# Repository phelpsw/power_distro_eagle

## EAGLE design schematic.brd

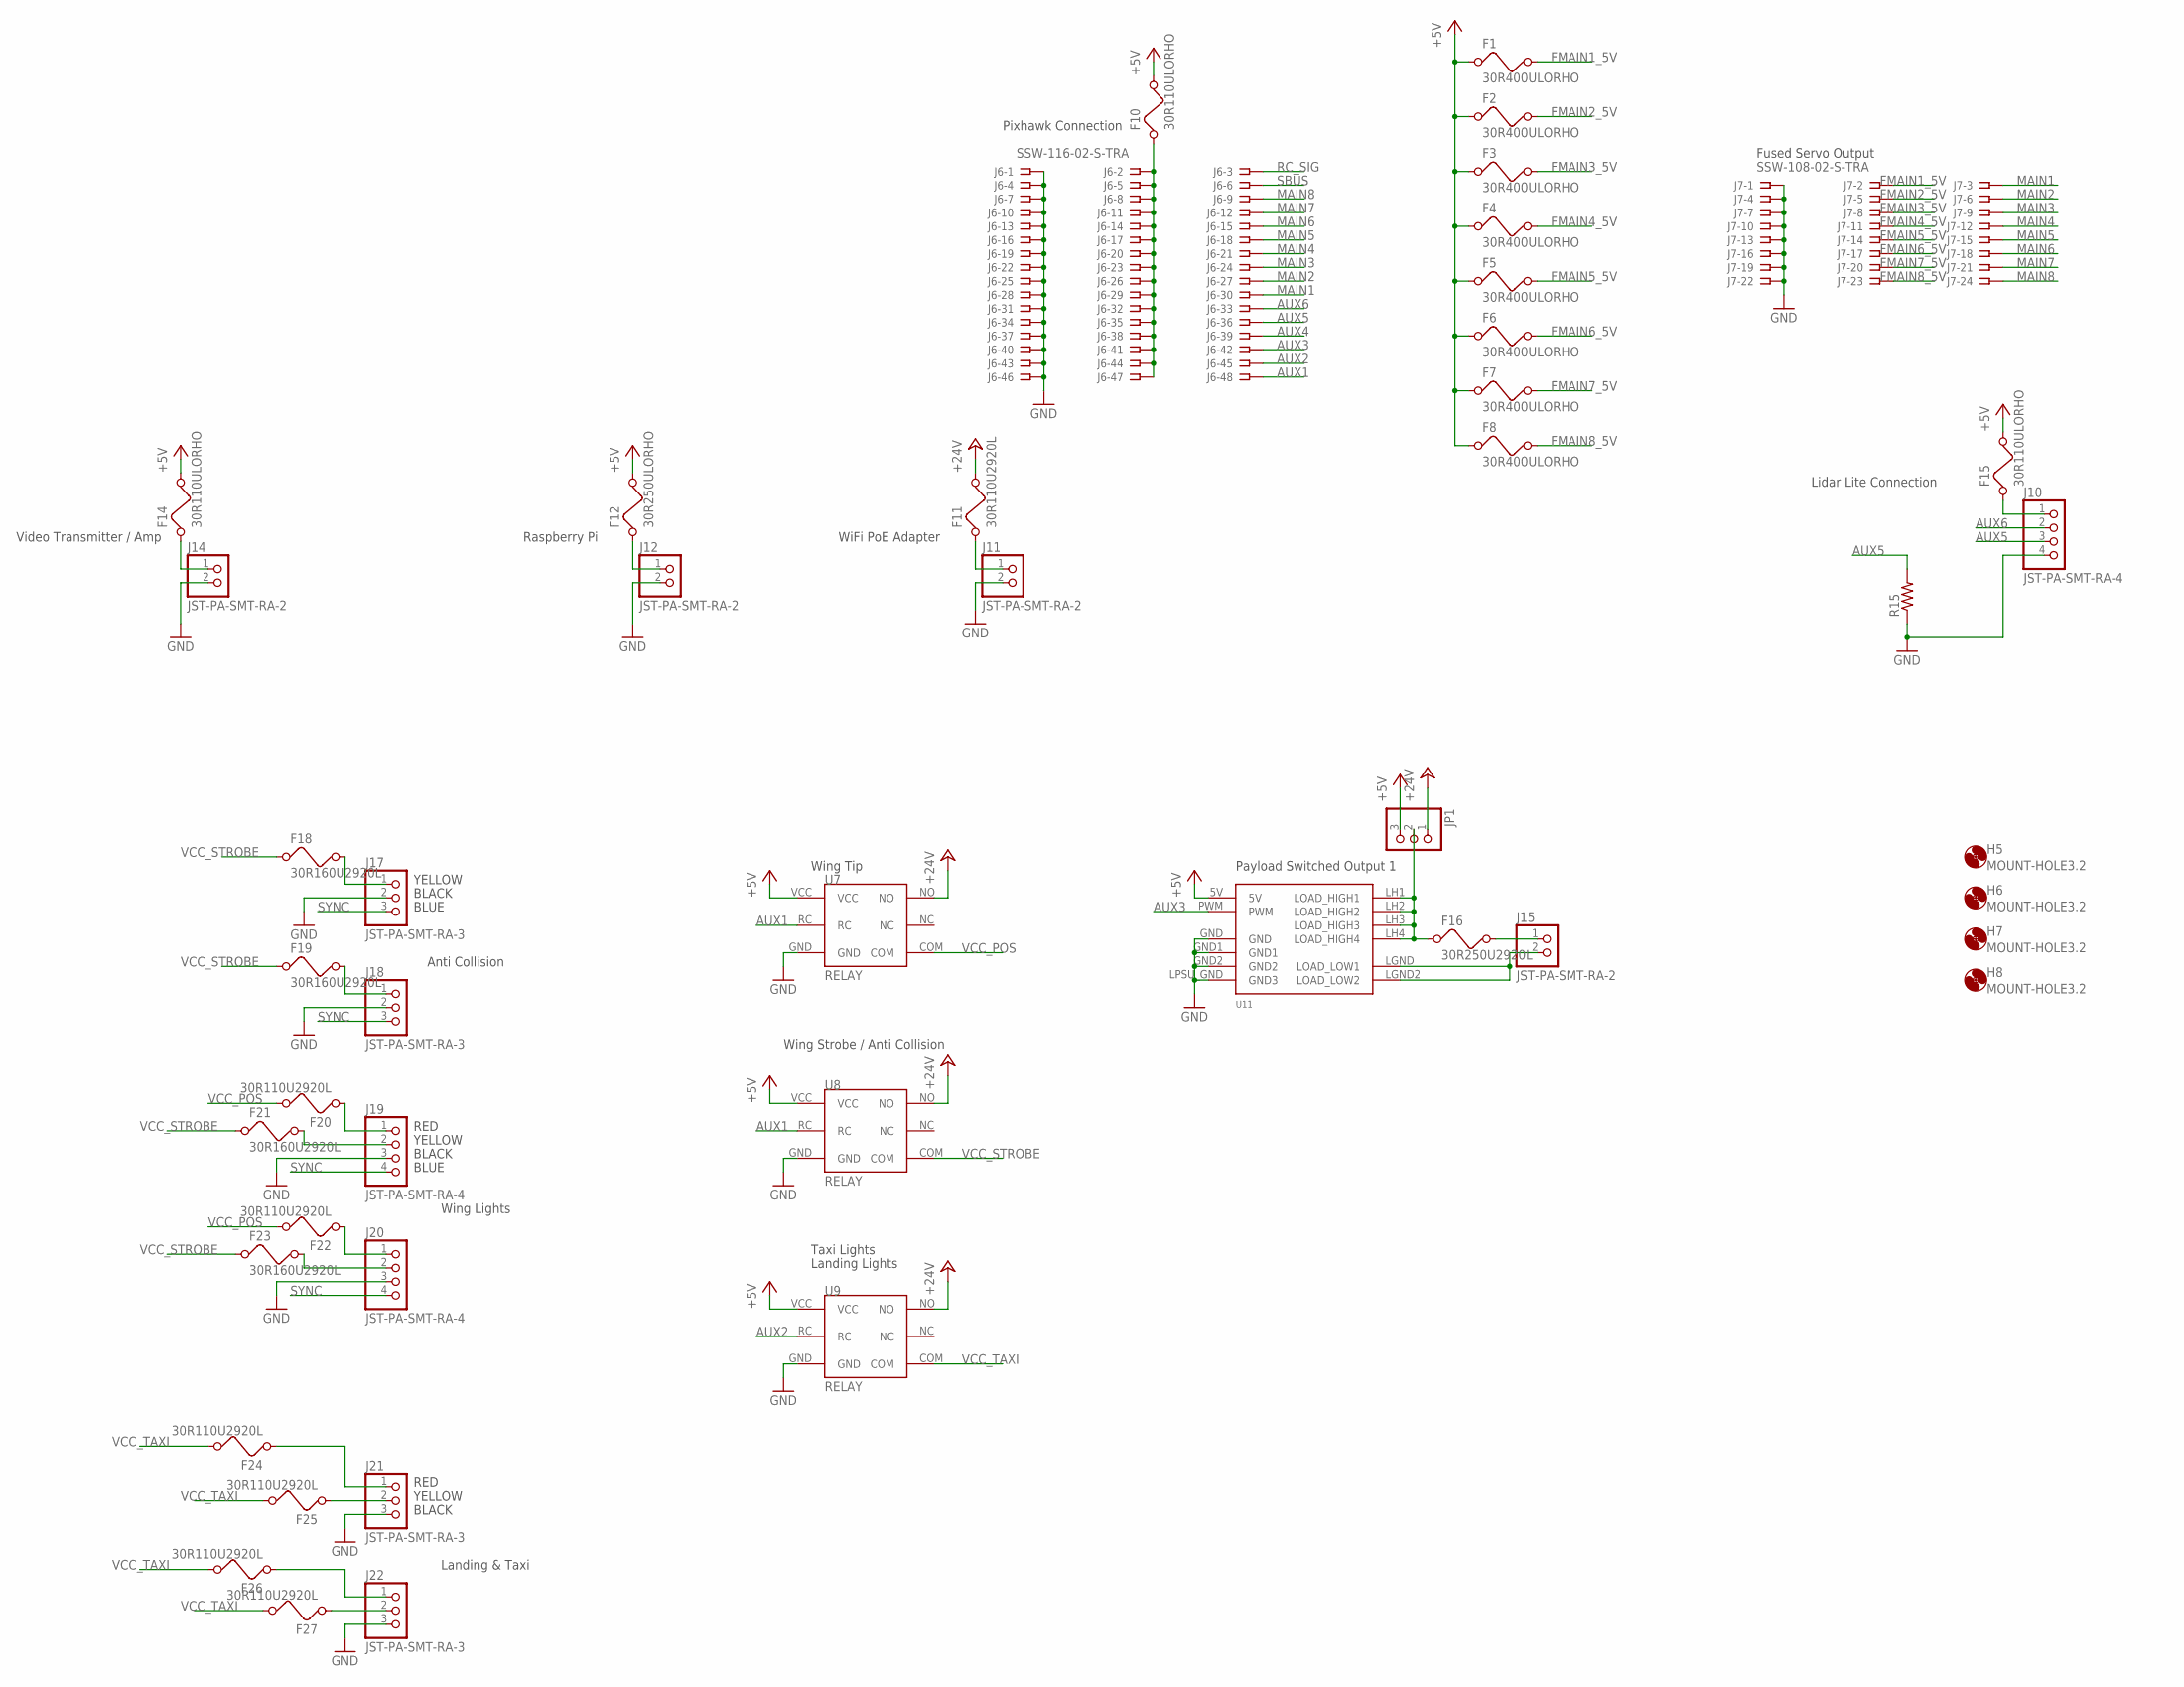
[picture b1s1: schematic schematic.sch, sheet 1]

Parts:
F1, F2, F3, F4, F5, F6, F7, F8: 30R400ULORHO; 1206
F10, F14, F15: 30R110ULORHO; 1206
F11, F20, F22, F24, F25, F26, F27: 30R110U2920L; 2920L
F12: 30R250ULORHO; 1206
F16: 30R250U2920L; 2920L
F18, F19, F21, F23: 30R160U2920L; 2920L
H5, H6, H7, H8: MOUNT-HOLE3.2; 3,2
J6: SSW-116-02-S-TRA; SSW-116-02-S-T-RA
J7: SSW-108-02-S-TRA; SSW-108-02-S-T-RA
J10, J19, J20: JST-PA-SMT-RA-4
J11, J12, J14, J15: JST-PA-SMT-RA-2
J17, J18, J21, J22: JST-PA-SMT-RA-3
JP1: PINHD-1X3; 1X03
R15: R-US_M0805; M0805
U7, U8, U9: RELAY
U11: MED_MOSFET

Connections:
+5V: F1.1, F2.1, F3.1, F4.1, F5.1, F6.1, F7.1, F8.1, F10.2, F12.2, F14.2, F15.2, JP1.3, U7.VCC, U8.VCC, U9.VCC, U11.5V; also elsewhere on the board
+24V: F11.P$2 (2), JP1.1, U7.NO, U8.NO, U9.NO; also elsewhere on the board
AUX1: J6.48, U7.RC, U8.RC
AUX2: J6.45, U9.RC
AUX3: J6.42, U11.PWM
AUX4: J6.39
AUX5: J6.36, J10.3, R15.2
AUX6: J6.33, J10.2
FMAIN1_5V: F1.2, J7.2
FMAIN2_5V: F2.2, J7.5
FMAIN3_5V: F3.2, J7.8
FMAIN4_5V: F4.2, J7.11
FMAIN5_5V: F5.2, J7.14
FMAIN6_5V: F6.2, J7.17
FMAIN7_5V: F7.2, J7.20
FMAIN8_5V: F8.2, J7.23
GND: J6.1, J6.4, J6.7, J6.10, J6.13, J6.16, J6.19, J6.22, J6.25, J6.28, J6.31, J6.34, J6.37, J6.40, J6.43, J6.46, J7.1, J7.4, J7.7, J7.10, J7.13, J7.16, J7.19, J7.22, J10.4, J11.2, J12.2, J14.2, J17.2, J18.2, J19.3, J20.3, J21.3, J22.3, R15.1, U7.GND, U8.GND, U9.GND, U11.GND, U11.GND1, U11.GND2, U11.LPSU_GND (GND3); also elsewhere on the board
MAIN1: J6.30, J7.3
MAIN2: J6.27, J7.6
MAIN3: J6.24, J7.9
MAIN4: J6.21, J7.12
MAIN5: J6.18, J7.15
MAIN6: J6.15, J7.18
MAIN7: J6.12, J7.21
MAIN8: J6.9, J7.24
unnamed: F12.1, J12.1
unnamed: F15.1, J10.1
unnamed: F16.P$1 (1), JP1.2, U11.LH1 (LOAD_HIGH1), U11.LH2 (LOAD_HIGH2), U11.LH3 (LOAD_HIGH3), U11.LH4 (LOAD_HIGH4)
unnamed: F10.1, J6.2, J6.5, J6.8, J6.11, J6.14, J6.17, J6.20, J6.23, J6.26, J6.29, J6.32, J6.35, J6.38, J6.41, J6.44, J6.47
unnamed: F11.P$1 (1), J11.1
unnamed: F16.P$2 (2), J15.1
unnamed: J15.2, U11.LGND (LOAD_LOW1), U11.LGND2 (LOAD_LOW2)
unnamed: F14.1, J14.1
unnamed: F20.P$1 (1), J19.1
unnamed: F21.P$2 (2), J19.2
unnamed: F22.P$1 (1), J20.1
unnamed: F23.P$2 (2), J20.2
unnamed: F18.P$2 (2), J17.1
unnamed: F19.P$2 (2), J18.1
unnamed: F27.P$1 (1), J22.2
unnamed: F26.P$1 (1), J22.1
unnamed: F25.P$1 (1), J21.2
unnamed: F24.P$1 (1), J21.1
RC_SIG: J6.3; also elsewhere on the board
SBUS: J6.6
SYNC: J17.3, J18.3, J19.4, J20.4
VCC_POS: F20.P$2 (2), F22.P$2 (2), U7.COM
VCC_STROBE: F18.P$1 (1), F19.P$1 (1), F21.P$1 (1), F23.P$1 (1), U8.COM
VCC_TAXI: F24.P$2 (2), F25.P$2 (2), F26.P$2 (2), F27.P$2 (2), U9.COM

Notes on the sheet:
WiFi PoE Adapter
Payload Switched Output 1
Wing Tip
Wing Strobe / Anti Collision
Raspberry Pi
Pixhawk Connection
Fused Servo Output
Lidar Lite Connection
Video Transmitter / Amp
Wing Lights
Taxi Lights
Landing Lights
RED
YELLOW
BLACK
BLUE
Anti Collision
Landing & Taxi

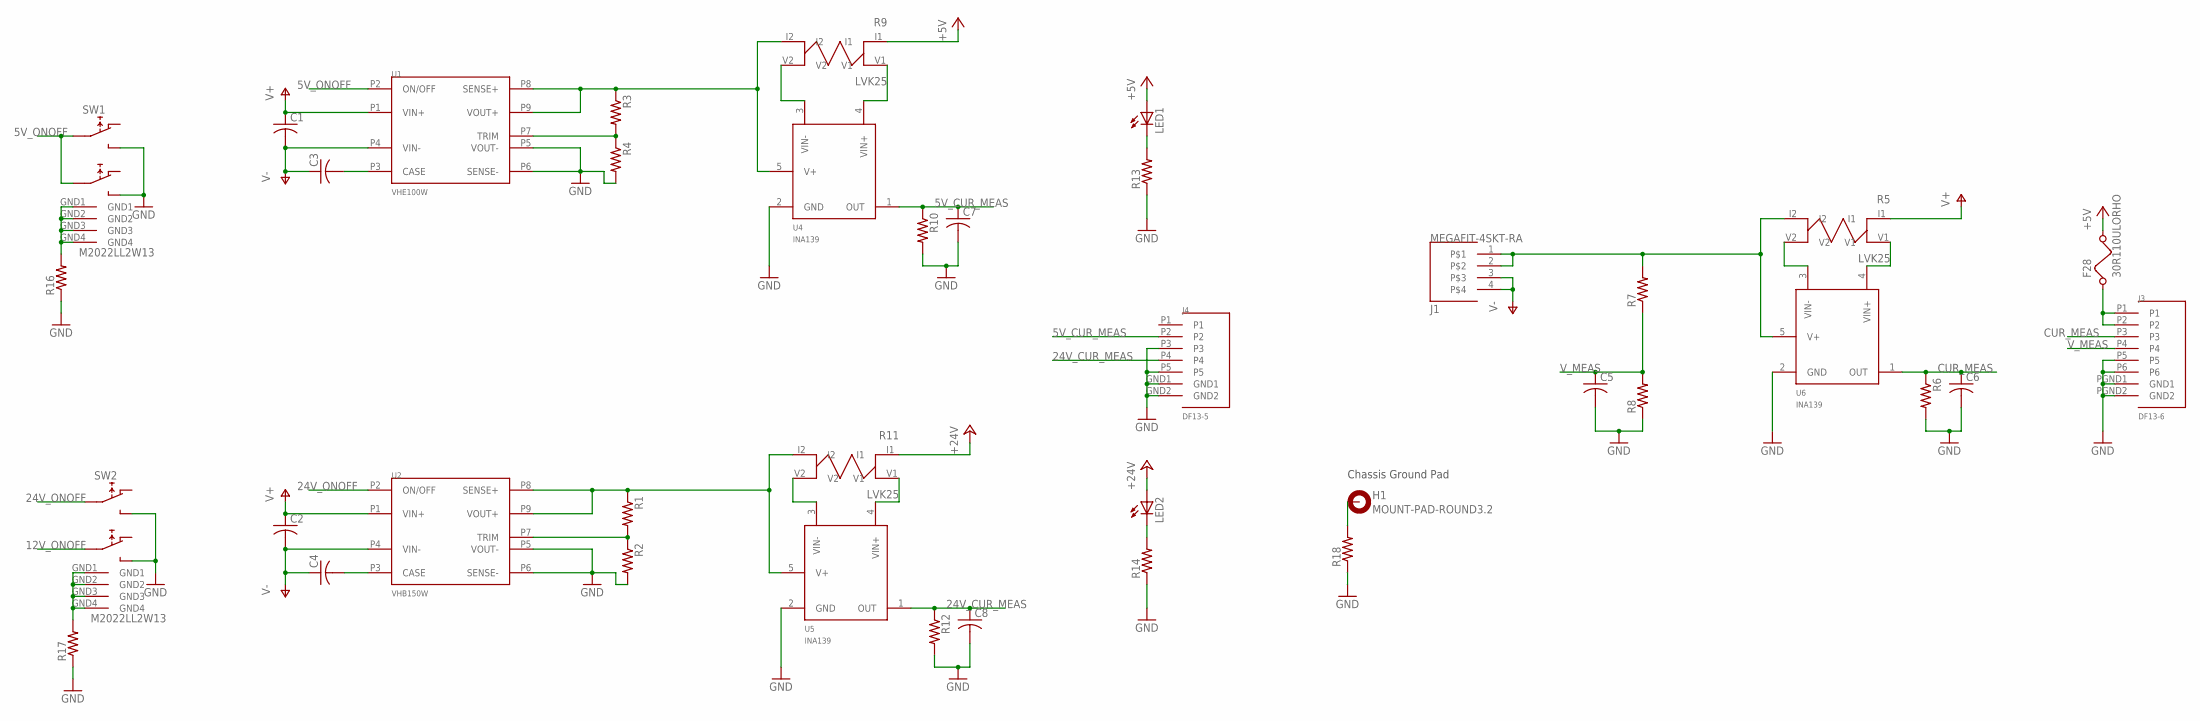
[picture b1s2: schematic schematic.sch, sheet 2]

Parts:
C1, C2, C3, C4: C-USC1210; C1210
C5, C6, C7, C8: C-USC0805; C0805
F28: 30R110ULORHO; 1206
H1: MOUNT-PAD-ROUND3.2; 3,2-PAD
J1: MEGAFIT-4SKT-RA
J3: DF13-6
J4: DF13-5
LED1, LED2: LEDCHIPLED_0805; CHIPLED_0805
R1, R2, R3, R4, R6, R7, R8, R10, R12, R13, R14, R16, R17, R18: R-US_M0805; M0805
R5, R9, R11: LVK25
SW1, SW2: M2022LL2W13
U1: VHE100W
U2: VHB150W
U4, U5, U6: INA139; SOT23-5

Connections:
5V_CUR_MEAS: C7.1, J4.P2, R10.1, U4.1 (OUT)
5V_ONOFF: SW1.P2 (1A), SW1.P5 (1A1), U1.P2 (ON/OFF)
12V_ONOFF: SW2.P5 (1A1)
24V_CUR_MEAS: C8.1, J4.P4, R12.1, U5.1 (OUT)
24V_ONOFF: SW2.P2 (1A), U2.P2 (ON/OFF)
+5V: F28.2, LED1.A, R9.I1; also elsewhere on the board
+24V: LED2.A, R11.I1; also elsewhere on the board
CUR_MEAS: C6.1, J3.P3, R6.1, U6.1 (OUT)
GND: C5.2, C6.2, C7.2, C8.2, J3.P5, J3.P6, J3.PGND1 (GND1), J3.PGND2 (GND2), J4.GND1, J4.GND2, J4.P3, J4.P5, R2.2, R4.2, R6.2, R8.1, R10.2, R12.2, R13.1, R14.1, R16.1, R17.1, R18.1, SW1.P1 (NO), SW1.P4 (NO1), SW2.P1 (NO), SW2.P4 (NO1), U1.P5 (VOUT-), U1.P6 (SENSE-), U2.P5 (VOUT-), U2.P6 (SENSE-), U4.2 (GND), U5.2 (GND), U6.2 (GND); also elsewhere on the board
unnamed: R1.2, R2.1, U2.P7 (TRIM)
unnamed: R3.2, R4.1, U1.P7 (TRIM)
unnamed: C3.2, U1.P3 (CASE)
unnamed: C4.2, U2.P3 (CASE)
unnamed: R9.V2, U4.3 (VIN-)
unnamed: R9.V1, U4.4 (VIN+)
unnamed: F28.1, J3.P1, J3.P2
unnamed: R11.V2, U5.3 (VIN-)
unnamed: LED2.C, R14.2
unnamed: LED1.C, R13.2
unnamed: R1.1, R11.I2, U2.P8 (SENSE+), U2.P9 (VOUT+), U5.5 (V+)
unnamed: R11.V1, U5.4 (VIN+)
unnamed: R3.1, R9.I2, U1.P8 (SENSE+), U1.P9 (VOUT+), U4.5 (V+)
unnamed: R5.V2, U6.3 (VIN-)
unnamed: J1.1, J1.2, R5.I2, R7.2, U6.5 (V+)
unnamed: R5.V1, U6.4 (VIN+)
unnamed: H1.B3,2, R18.2
unnamed: R17.2, SW2.GND1, SW2.GND2, SW2.GND3, SW2.GND4
unnamed: R16.2, SW1.GND1, SW1.GND2, SW1.GND3, SW1.GND4
V+: C1.1, C2.1, R5.I1, U1.P1 (VIN+), U2.P1 (VIN+)
V-: C1.2, C2.2, C3.1, C4.1, J1.3, J1.4, U1.P4 (VIN-), U2.P4 (VIN-)
V_MEAS: C5.1, J3.P4, R7.1, R8.2

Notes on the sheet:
Chassis Ground Pad

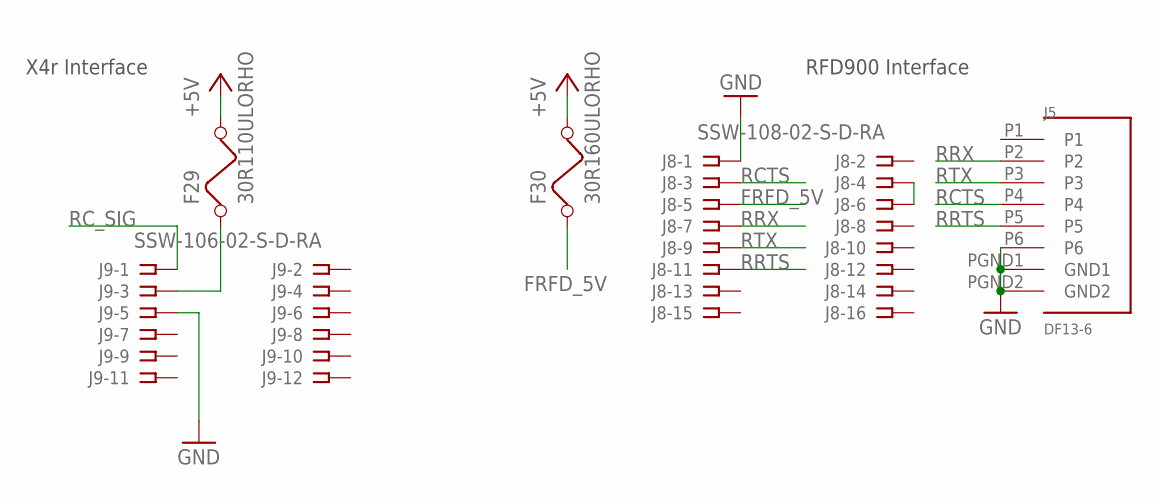
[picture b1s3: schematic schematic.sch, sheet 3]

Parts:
F29: 30R110ULORHO; 1206
F30: 30R160ULORHO; 1206
J5: DF13-6
J8: SSW-108-02-S-D-RA; TSW-108-02-S-D-RA
J9: SSW-106-02-S-D-RA; TSW-106-02-S-D-RA

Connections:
+5V: F29.2, F30.2; also elsewhere on the board
FRFD_5V: F30.1, J8.5
GND: J5.P6, J5.PGND1 (GND1), J5.PGND2 (GND2), J8.1, J9.5; also elsewhere on the board
unnamed: F29.1, J9.3
unnamed: J8.4, J8.6
RCTS: J5.P4, J8.3
RC_SIG: J9.1; also elsewhere on the board
RRTS: J5.P5, J8.11
RRX: J5.P2, J8.7
RTX: J5.P3, J8.9

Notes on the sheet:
X4r Interface
RFD900 Interface

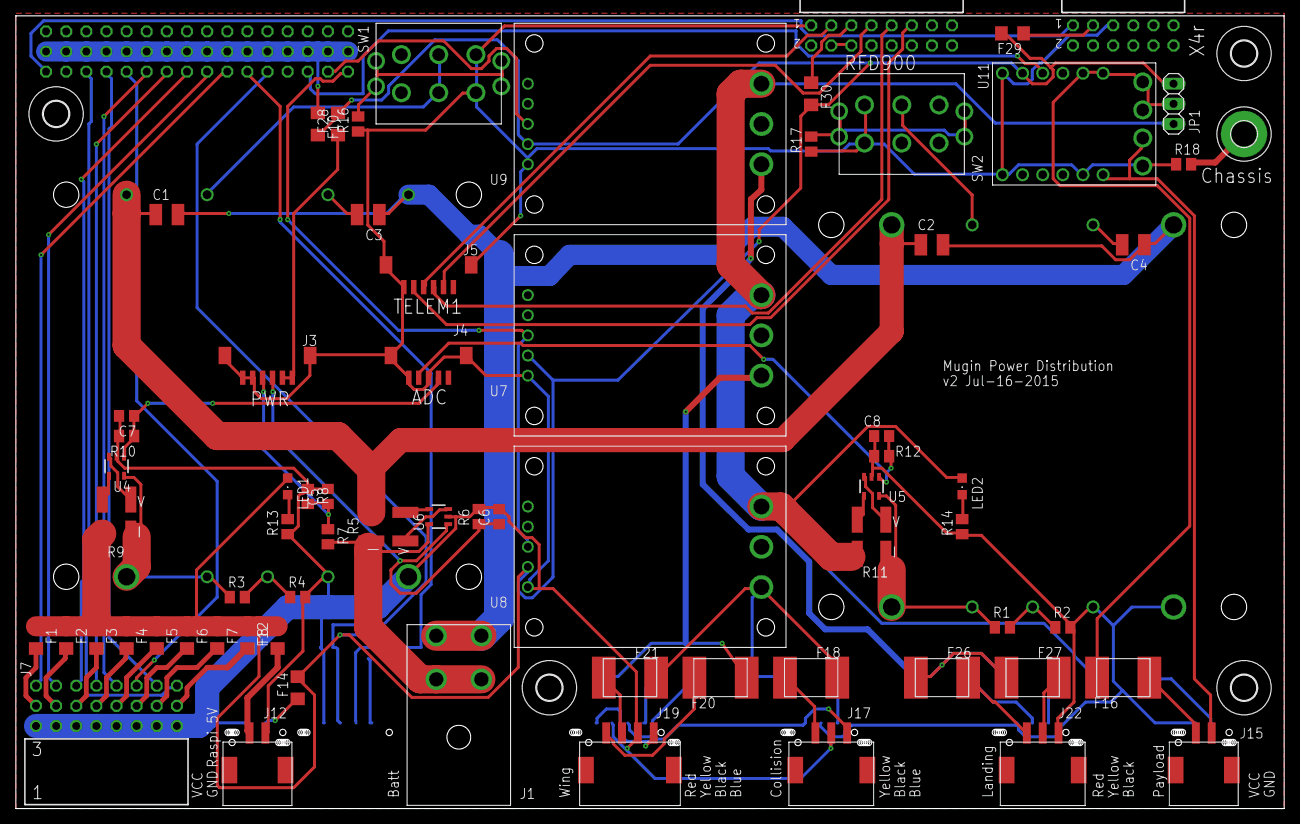
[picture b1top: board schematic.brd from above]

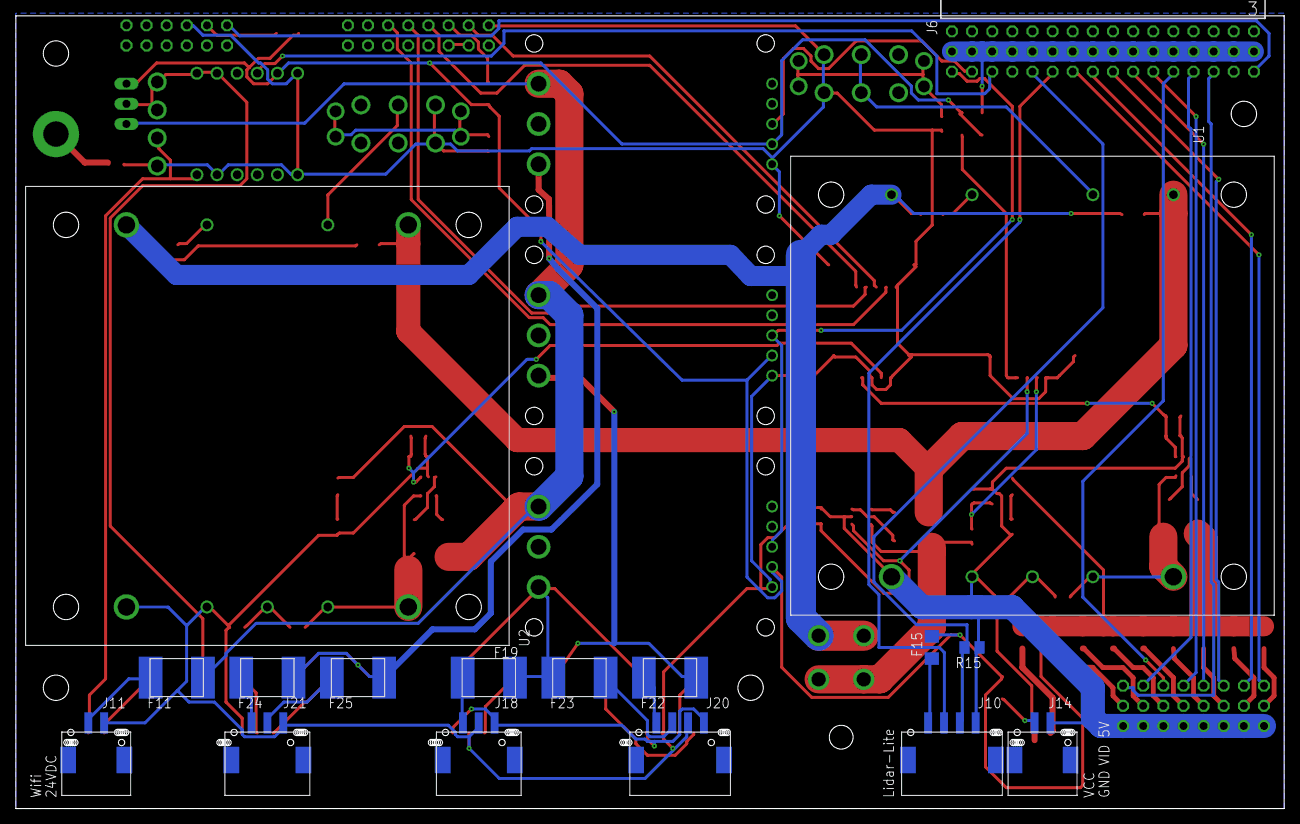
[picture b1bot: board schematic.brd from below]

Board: 2 copper layers, 160.0 x 100.0 mm, 91 parts (17 on the bottom side), 81 nets.

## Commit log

2015-06-23 Preliminary version.
2015-06-23 Adding board.
2015-06-27 Connectorizing and adding switches.
2015-07-03 Connecting power connectors and lidar lite.
2015-07-03 Adding 12v rail and connecting payloads.
2015-07-06 Adding new power connector.
2015-07-07 Removing some components space doesn't allow for. Established basic layout.
2015-07-10 Updating drawing with new right angle connectors on a single board side.
2015-07-11 Adding some 5v ptc smt devices instead of the big throughhole units.
2015-07-13 Updated so all fuses are SMT.
2015-07-13 Basic text, pre autoroute.
2015-07-14 Power traces run, remainder are low current and can be autorouted.
2015-07-15 Silkscreen adjustments, cleanup prior to autoroute.
2015-07-15 Autorouted and ground plane poured.
2015-07-15 DRC checks completed.
2015-07-15 Rotating pixhawk so the df13 connectors on that board and on top. Autorouting signals after flipping.
2015-07-15 Breaking up schematic into another page.
2015-07-16 Adding gitignore with common temp files generated by eagle.
